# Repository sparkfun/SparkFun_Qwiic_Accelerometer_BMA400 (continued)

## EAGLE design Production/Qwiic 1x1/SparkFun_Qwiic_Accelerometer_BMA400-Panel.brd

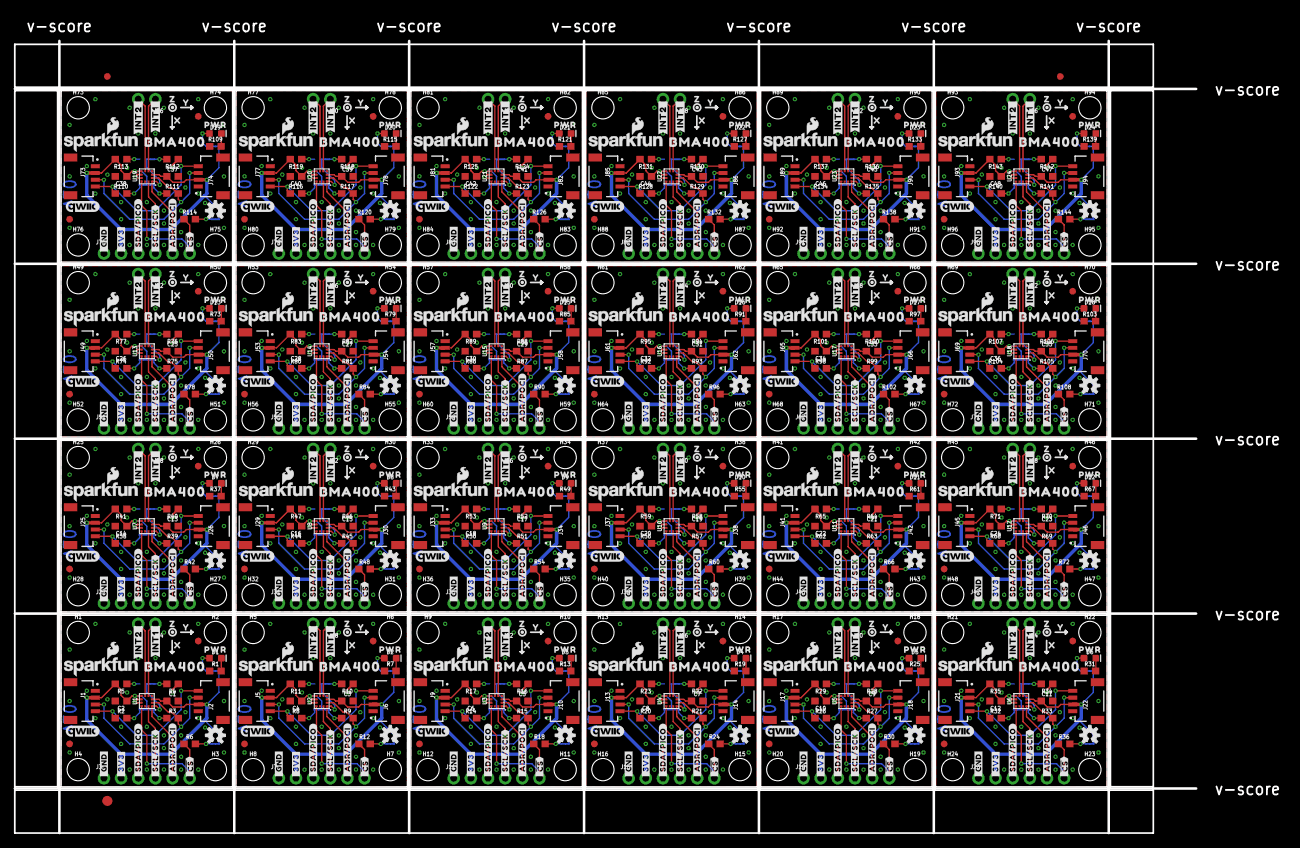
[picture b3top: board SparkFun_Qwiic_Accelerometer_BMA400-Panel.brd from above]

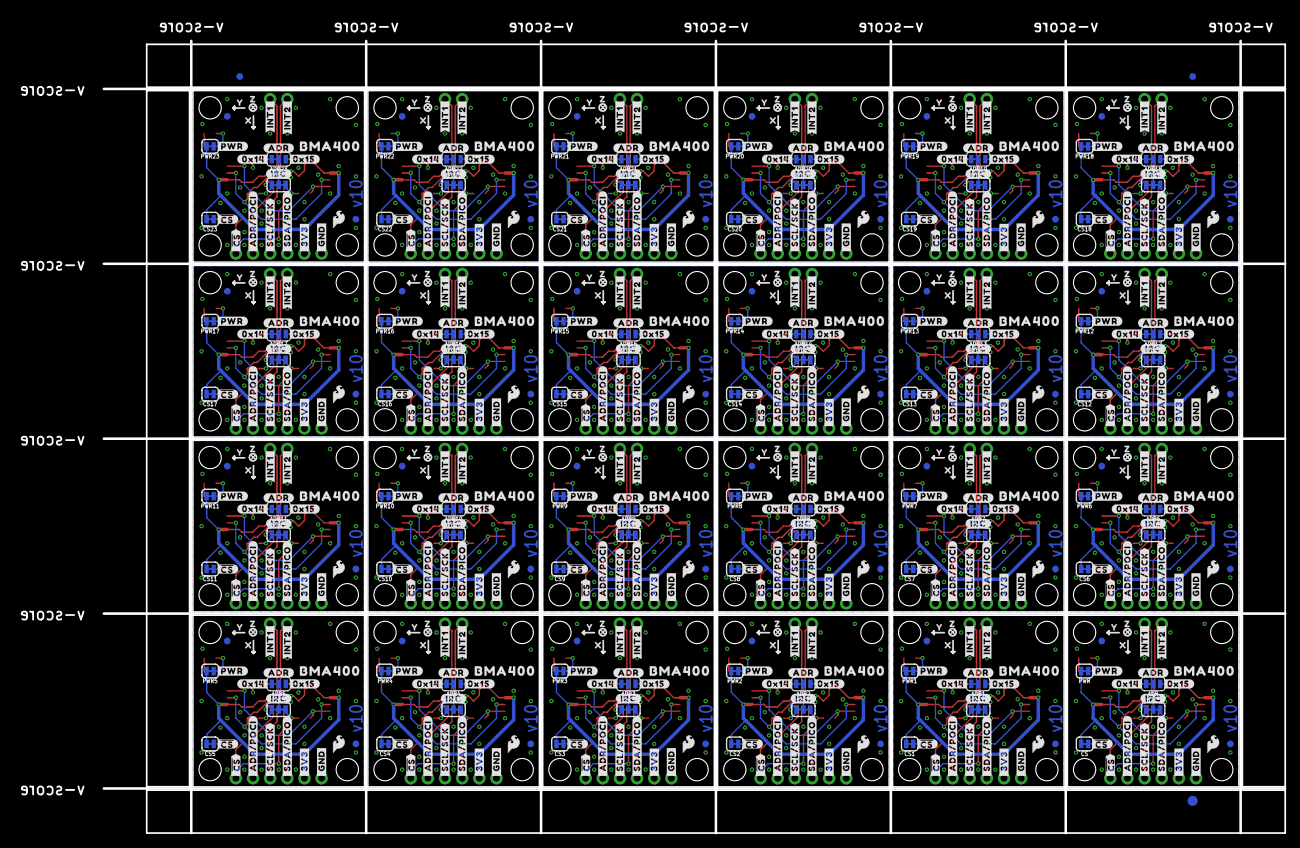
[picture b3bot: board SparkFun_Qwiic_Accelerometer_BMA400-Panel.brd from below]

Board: 2 copper layers, 175.0 x 117.3 mm, 1470 parts (603 on the bottom side), 360 nets.

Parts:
!CS!, !CS!1, !CS!2, !CS!3, !CS!4, !CS!5, !CS!6, !CS!7, !CS!8, !CS!9, !CS!10, !CS!11, !CS!12, !CS!13, !CS!14, !CS!15, !CS!16, !CS!17, !CS!18, !CS!19, !CS!20, !CS!21, !CS!22, !CS!23: JUMPER-SMT_2_NC_TRACE_SILK; SMT-JUMPER_2_NC_TRACE_SILK
ADR, ADR1, ADR2, ADR3, ADR4, ADR5, ADR6, ADR7, ADR8, ADR9, ADR10, ADR11, ADR12, ADR13, ADR14, ADR15, ADR16, ADR17, ADR18, ADR19, ADR20, ADR21, ADR22, ADR23: JUMPER-SMT_3_1-NC_TRACE_SILK; SMT-JUMPER_3_1-NC_TRACE_SILK
C1, C2, C3, C4, C5, C6, C7, C8, C9, C10, C11, C12, C13, C14, C15, C16, C17, C18, C19, C20, C21, C22, C23, C24, C25, C26, C27, C28, C29, C30, C31, C32, C33, C34, C35, C36, C37, C38, C39, C40, C41, C42, C43, C44, C45, C46, C47, C48: 0.1uF; 0603
D1, D2, D3, D4, D5, D6, D7, D8, D9, D10, D11, D12, D13, D14, D15, D16, D17, D18, D19, D20, D21, D22, D23, D24: RED; LED-0603
E$1, E$2, E$3, E$4: FIDUCIAL-1X2
E$5, E$6: FIDUCIAL-1.5X3
FD1, FD2, FD3, FD4, FD5, FD6, FD7, FD8, FD9, FD10, FD11, FD12, FD13, FD14, FD15, FD16, FD17, FD18, FD19, FD20, FD21, FD22, FD23, FD24, FD25, FD26, FD27, FD28, FD29, FD30, FD31, FD32, FD33, FD34, FD35, FD36, FD37, FD38, FD39, FD40, FD41, FD42, FD43, FD44, FD45, FD46, FD47, FD48, FD49, FD50, FD51, FD52, FD53, FD54, FD55, FD56, FD57, FD58, FD59, FD60, FD61, FD62, FD63, FD64, FD65, FD66, FD67, FD68, FD69, FD70, FD71, FD72, FD73, FD74, FD75, FD76, FD77, FD78, FD79, FD80, FD81, FD82, FD83, FD84, FD85, FD86, FD87, FD88, FD89, FD90, FD91, FD92, FD93, FD94, FD95, FD96: FIDUCIAL1X2; FIDUCIAL-1X2
H1, H2, H3, H4, H5, H6, H7, H8, H9, H10, H11, H12, H13, H14, H15, H16, H17, H18, H19, H20, H21, H22, H23, H24, H25, H26, H27, H28, H29, H30, H31, H32, H33, H34, H35, H36, H37, H38, H39, H40, H41, H42, H43, H44, H45, H46, H47, H48, H49, H50, H51, H52, H53, H54, H55, H56, H57, H58, H59, H60, H61, H62, H63, H64, H65, H66, H67, H68, H69, H70, H71, H72, H73, H74, H75, H76, H77, H78, H79, H80, H81, H82, H83, H84, H85, H86, H87, H88, H89, H90, H91, H92, H93, H94, H95, H96: STAND-OFF
I2C, I2C1, I2C2, I2C3, I2C4, I2C5, I2C6, I2C7, I2C8, I2C9, I2C10, I2C11, I2C12, I2C13, I2C14, I2C15, I2C16, I2C17, I2C18, I2C19, I2C20, I2C21, I2C22, I2C23: JUMPER-SMT_3_2-NC_TRACE_SILK; SMT-JUMPER_3_2-NC_TRACE_SILK
J1, J2, J5, J6, J9, J10, J13, J14, J17, J18, J21, J22, J25, J26, J29, J30, J33, J34, J37, J38, J41, J42, J45, J46, J49, J50, J53, J54, J57, J58, J61, J62, J65, J66, J69, J70, J73, J74, J77, J78, J81, J82, J85, J86, J89, J90, J93, J94: QWIIC_RIGHT_ANGLE; JST04_1MM_RA
J3, J7, J11, J15, J19, J23, J27, J31, J35, J39, J43, J47, J51, J55, J59, J63, J67, J71, J75, J79, J83, J87, J91, J95: 1X06_NO_SILK
J4, J8, J12, J16, J20, J24, J28, J32, J36, J40, J44, J48, J52, J56, J60, J64, J68, J72, J76, J80, J84, J88, J92, J96: 1X02_NO_SILK
LOGO1, LOGO4, LOGO7, LOGO10, LOGO13, LOGO16, LOGO19, LOGO22, LOGO25, LOGO28, LOGO31, LOGO34, LOGO37, LOGO40, LOGO43, LOGO46, LOGO49, LOGO52, LOGO55, LOGO58, LOGO61, LOGO64, LOGO67, LOGO70: QWIIC_LOGO_5MM; QWIIC_5MM
LOGO2, LOGO5, LOGO8, LOGO11, LOGO14, LOGO17, LOGO20, LOGO23, LOGO26, LOGO29, LOGO32, LOGO35, LOGO38, LOGO41, LOGO44, LOGO47, LOGO50, LOGO53, LOGO56, LOGO59, LOGO62, LOGO65, LOGO68, LOGO71: SFE_LOGO_NAME_FLAME.1_INCH; SFE_LOGO_NAME_FLAME_.1
LOGO3, LOGO6, LOGO9, LOGO12, LOGO15, LOGO18, LOGO21, LOGO24, LOGO27, LOGO30, LOGO33, LOGO36, LOGO39, LOGO42, LOGO45, LOGO48, LOGO51, LOGO54, LOGO57, LOGO60, LOGO63, LOGO66, LOGO69, LOGO72: OSHW-LOGOS; OSHW-LOGO-S
PWR, PWR1, PWR2, PWR3, PWR4, PWR5, PWR6, PWR7, PWR8, PWR9, PWR10, PWR11, PWR12, PWR13, PWR14, PWR15, PWR16, PWR17, PWR18, PWR19, PWR20, PWR21, PWR22, PWR23: JUMPER-SMT_2_NC_TRACE_SILK; SMT-JUMPER_2_NC_TRACE_SILK
R1, R7, R13, R19, R25, R31, R37, R43, R49, R55, R61, R67, R73, R79, R85, R91, R97, R103, R109, R115, R121, R127, R133, R139: 1k; 0603
R2, R3, R8, R9, R14, R15, R20, R21, R26, R27, R32, R33, R38, R39, R44, R45, R50, R51, R56, R57, R62, R63, R68, R69, R74, R75, R80, R81, R86, R87, R92, R93, R98, R99, R104, R105, R110, R111, R116, R117, R122, R123, R128, R129, R134, R135, R140, R141: 2.2k; 0603
R4, R5, R6, R10, R11, R12, R16, R17, R18, R22, R23, R24, R28, R29, R30, R34, R35, R36, R40, R41, R42, R46, R47, R48, R52, R53, R54, R58, R59, R60, R64, R65, R66, R70, R71, R72, R76, R77, R78, R82, R83, R84, R88, R89, R90, R94, R95, R96, R100, R101, R102, R106, R107, R108, R112, R113, R114, R118, R119, R120, R124, R125, R126, R130, R131, R132, R136, R137, R138, R142, R143, R144: 10k; 0603
U1, U2, U3, U4, U5, U6, U7, U8, U9, U10, U11, U12, U13, U14, U15, U16, U17, U18, U19, U20, U21, U22, U23, U24: BMA400
U$1, U$30, U$65, U$97, U$129, U$161, U$193, U$225, U$257, U$289, U$321, U$353, U$385, U$417, U$449, U$481, U$513, U$545, U$577, U$609, U$641, U$673, U$705, U$737: PWR0
U$2, U$34, U$59, U$62, U$91, U$94, U$123, U$126, U$155, U$158, U$187, U$190, U$219, U$222, U$251, U$254, U$283, U$286, U$315, U$318, U$347, U$350, U$379, U$382, U$411, U$414, U$443, U$446, U$475, U$478, U$507, U$510, U$539, U$542, U$571, U$574, U$603, U$606, U$635, U$638, U$667, U$670, U$699, U$702, U$731, U$734, U$763, U$766: X2114
U$3, U$35, U$60, U$63, U$92, U$95, U$124, U$127, U$156, U$159, U$188, U$191, U$220, U$223, U$252, U$255, U$284, U$287, U$316, U$319, U$348, U$351, U$380, U$383, U$412, U$415, U$444, U$447, U$476, U$479, U$508, U$511, U$540, U$543, U$572, U$575, U$604, U$607, U$636, U$639, U$668, U$671, U$700, U$703, U$732, U$735, U$764, U$767: Y2115
U$4, U$20, U$31, U$46, U$66, U$78, U$98, U$110, U$130, U$142, U$162, U$174, U$194, U$206, U$226, U$238, U$258, U$270, U$290, U$302, U$322, U$334, U$354, U$366, U$386, U$398, U$418, U$430, U$450, U$462, U$482, U$494, U$514, U$526, U$546, U$558, U$578, U$590, U$610, U$622, U$642, U$654, U$674, U$686, U$706, U$718, U$738, U$750: #INT1_#0
U$5, U$21, U$32, U$47, U$67, U$79, U$99, U$111, U$131, U$143, U$163, U$175, U$195, U$207, U$227, U$239, U$259, U$271, U$291, U$303, U$323, U$335, U$355, U$367, U$387, U$399, U$419, U$431, U$451, U$463, U$483, U$495, U$515, U$527, U$547, U$559, U$579, U$591, U$611, U$623, U$643, U$655, U$675, U$687, U$707, U$719, U$739, U$751: #INT2_#0
U$6, U$57, U$89, U$121, U$153, U$185, U$217, U$249, U$281, U$313, U$345, U$377, U$409, U$441, U$473, U$505, U$537, U$569, U$601, U$633, U$665, U$697, U$729, U$761: #_3V3#6
U$7, U$56, U$88, U$120, U$152, U$184, U$216, U$248, U$280, U$312, U$344, U$376, U$408, U$440, U$472, U$504, U$536, U$568, U$600, U$632, U$664, U$696, U$728, U$760: #_SDA#PICO#5
U$8, U$54, U$86, U$118, U$150, U$182, U$214, U$246, U$278, U$310, U$342, U$374, U$406, U$438, U$470, U$502, U$534, U$566, U$598, U$630, U$662, U$694, U$726, U$758: #_#CS##2
U$9, U$55, U$87, U$119, U$151, U$183, U$215, U$247, U$279, U$311, U$343, U$375, U$407, U$439, U$471, U$503, U$535, U$567, U$599, U$631, U$663, U$695, U$727, U$759: #_SCL#SCK#3
U$10, U$33, U$68, U$100, U$132, U$164, U$196, U$228, U$260, U$292, U$324, U$356, U$388, U$420, U$452, U$484, U$516, U$548, U$580, U$612, U$644, U$676, U$708, U$740: #_GND#0
U$11, U$37, U$69, U$101, U$133, U$165, U$197, U$229, U$261, U$293, U$325, U$357, U$389, U$421, U$453, U$485, U$517, U$549, U$581, U$613, U$645, U$677, U$709, U$741: #_3V3#0
U$12, U$38, U$70, U$102, U$134, U$166, U$198, U$230, U$262, U$294, U$326, U$358, U$390, U$422, U$454, U$486, U$518, U$550, U$582, U$614, U$646, U$678, U$710, U$742: #_SDA#PICO#0
U$13, U$39, U$71, U$103, U$135, U$167, U$199, U$231, U$263, U$295, U$327, U$359, U$391, U$423, U$455, U$487, U$519, U$551, U$583, U$615, U$647, U$679, U$711, U$743: #_SCL#SCK#0
U$14, U$40, U$72, U$104, U$136, U$168, U$200, U$232, U$264, U$296, U$328, U$360, U$392, U$424, U$456, U$488, U$520, U$552, U$584, U$616, U$648, U$680, U$712, U$744: #_ADR#POCI#0
U$15, U$41, U$73, U$105, U$137, U$169, U$201, U$233, U$265, U$297, U$329, U$361, U$393, U$425, U$457, U$489, U$521, U$553, U$585, U$617, U$649, U$681, U$713, U$745: #_#CS##0
U$16, U$42, U$74, U$106, U$138, U$170, U$202, U$234, U$266, U$298, U$330, U$362, U$394, U$426, U$458, U$490, U$522, U$554, U$586, U$618, U$650, U$682, U$714, U$746: #I2C#0
U$17, U$43, U$75, U$107, U$139, U$171, U$203, U$235, U$267, U$299, U$331, U$363, U$395, U$427, U$459, U$491, U$523, U$555, U$587, U$619, U$651, U$683, U$715, U$747: #ADR#0
U$18, U$44, U$76, U$108, U$140, U$172, U$204, U$236, U$268, U$300, U$332, U$364, U$396, U$428, U$460, U$492, U$524, U$556, U$588, U$620, U$652, U$684, U$716, U$748: #0X15#0
U$19, U$45, U$77, U$109, U$141, U$173, U$205, U$237, U$269, U$301, U$333, U$365, U$397, U$429, U$461, U$493, U$525, U$557, U$589, U$621, U$653, U$685, U$717, U$749: #0X14#0
U$22, U$48, U$80, U$112, U$144, U$176, U$208, U$240, U$272, U$304, U$336, U$368, U$400, U$432, U$464, U$496, U$528, U$560, U$592, U$624, U$656, U$688, U$720, U$752: #PWR#0
U$23, U$24, U$49, U$50, U$81, U$82, U$113, U$114, U$145, U$146, U$177, U$178, U$209, U$210, U$241, U$242, U$273, U$274, U$305, U$306, U$337, U$338, U$369, U$370, U$401, U$402, U$433, U$434, U$465, U$466, U$497, U$498, U$529, U$530, U$561, U$562, U$593, U$594, U$625, U$626, U$657, U$658, U$689, U$690, U$721, U$722, U$753, U$754: BMA4000
U$25, U$51, U$83, U$115, U$147, U$179, U$211, U$243, U$275, U$307, U$339, U$371, U$403, U$435, U$467, U$499, U$531, U$563, U$595, U$627, U$659, U$691, U$723, U$755: ##CS##0
U$26, U$52, U$84, U$116, U$148, U$180, U$212, U$244, U$276, U$308, U$340, U$372, U$404, U$436, U$468, U$500, U$532, U$564, U$596, U$628, U$660, U$692, U$724, U$756: SFE_LOGO_FLAME_.1
U$27, U$53, U$85, U$117, U$149, U$181, U$213, U$245, U$277, U$309, U$341, U$373, U$405, U$437, U$469, U$501, U$533, U$565, U$597, U$629, U$661, U$693, U$725, U$757: #_ADR#POCI#1
U$28, U$58, U$90, U$122, U$154, U$186, U$218, U$250, U$282, U$314, U$346, U$378, U$410, U$442, U$474, U$506, U$538, U$570, U$602, U$634, U$666, U$698, U$730, U$762: #_GND#6
U$29, U$36, U$61, U$64, U$93, U$96, U$125, U$128, U$157, U$160, U$189, U$192, U$221, U$224, U$253, U$256, U$285, U$288, U$317, U$320, U$349, U$352, U$381, U$384, U$413, U$416, U$445, U$448, U$477, U$480, U$509, U$512, U$541, U$544, U$573, U$576, U$605, U$608, U$637, U$640, U$669, U$672, U$701, U$704, U$733, U$736, U$765, U$768: Z2116

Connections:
3.3V: !CS!.2, C1.1, C2.1, I2C.2, J1.2, J2.2, J3.2, PWR.2, R5.2, U1.3, U1.7
3.3V1: !CS!1.2, C3.1, C4.1, I2C1.2, J5.2, J6.2, J7.2, PWR1.2, R11.2, U2.3, U2.7
3.3V2: !CS!2.2, C5.1, C6.1, I2C2.2, J9.2, J10.2, J11.2, PWR2.2, R17.2, U3.3, U3.7
3.3V3: !CS!3.2, C7.1, C8.1, I2C3.2, J13.2, J14.2, J15.2, PWR3.2, R23.2, U4.3, U4.7
3.3V4: !CS!4.2, C9.1, C10.1, I2C4.2, J17.2, J18.2, J19.2, PWR4.2, R29.2, U5.3, U5.7
3.3V5: !CS!5.2, C11.1, C12.1, I2C5.2, J21.2, J22.2, J23.2, PWR5.2, R35.2, U6.3, U6.7
3.3V6: !CS!6.2, C13.1, C14.1, I2C6.2, J25.2, J26.2, J27.2, PWR6.2, R41.2, U7.3, U7.7
3.3V7: !CS!7.2, C15.1, C16.1, I2C7.2, J29.2, J30.2, J31.2, PWR7.2, R47.2, U8.3, U8.7
3.3V8: !CS!8.2, C17.1, C18.1, I2C8.2, J33.2, J34.2, J35.2, PWR8.2, R53.2, U9.3, U9.7
3.3V9: !CS!9.2, C19.1, C20.1, I2C9.2, J37.2, J38.2, J39.2, PWR9.2, R59.2, U10.3, U10.7
3.3V10: !CS!10.2, C21.1, C22.1, I2C10.2, J41.2, J42.2, J43.2, PWR10.2, R65.2, U11.3, U11.7
3.3V11: !CS!11.2, C23.1, C24.1, I2C11.2, J45.2, J46.2, J47.2, PWR11.2, R71.2, U12.3, U12.7
3.3V12: !CS!12.2, C25.1, C26.1, I2C12.2, J49.2, J50.2, J51.2, PWR12.2, R77.2, U13.3, U13.7
3.3V13: !CS!13.2, C27.1, C28.1, I2C13.2, J53.2, J54.2, J55.2, PWR13.2, R83.2, U14.3, U14.7
3.3V14: !CS!14.2, C29.1, C30.1, I2C14.2, J57.2, J58.2, J59.2, PWR14.2, R89.2, U15.3, U15.7
3.3V15: !CS!15.2, C31.1, C32.1, I2C15.2, J61.2, J62.2, J63.2, PWR15.2, R95.2, U16.3, U16.7
3.3V16: !CS!16.2, C33.1, C34.1, I2C16.2, J65.2, J66.2, J67.2, PWR16.2, R101.2, U17.3, U17.7
3.3V17: !CS!17.2, C35.1, C36.1, I2C17.2, J69.2, J70.2, J71.2, PWR17.2, R107.2, U18.3, U18.7
3.3V18: !CS!18.2, C37.1, C38.1, I2C18.2, J73.2, J74.2, J75.2, PWR18.2, R113.2, U19.3, U19.7
3.3V19: !CS!19.2, C39.1, C40.1, I2C19.2, J77.2, J78.2, J79.2, PWR19.2, R119.2, U20.3, U20.7
3.3V20: !CS!20.2, C41.1, C42.1, I2C20.2, J81.2, J82.2, J83.2, PWR20.2, R125.2, U21.3, U21.7
3.3V21: !CS!21.2, C43.1, C44.1, I2C21.2, J85.2, J86.2, J87.2, PWR21.2, R131.2, U22.3, U22.7
3.3V22: !CS!22.2, C45.1, C46.1, I2C22.2, J89.2, J90.2, J91.2, PWR22.2, R137.2, U23.3, U23.7
3.3V23: !CS!23.2, C47.1, C48.1, I2C23.2, J93.2, J94.2, J95.2, PWR23.2, R143.2, U24.3, U24.7
!CS!: J3.6, R6.1, U1.10
!CS!1: J7.6, R12.1, U2.10
!CS!2: J11.6, R18.1, U3.10
!CS!3: J15.6, R24.1, U4.10
!CS!4: J19.6, R30.1, U5.10
!CS!5: J23.6, R36.1, U6.10
!CS!6: J27.6, R42.1, U7.10
!CS!7: J31.6, R48.1, U8.10
!CS!8: J35.6, R54.1, U9.10
!CS!9: J39.6, R60.1, U10.10
!CS!10: J43.6, R66.1, U11.10
!CS!11: J47.6, R72.1, U12.10
!CS!12: J51.6, R78.1, U13.10
!CS!13: J55.6, R84.1, U14.10
!CS!14: J59.6, R90.1, U15.10
!CS!15: J63.6, R96.1, U16.10
!CS!16: J67.6, R102.1, U17.10
!CS!17: J71.6, R108.1, U18.10
!CS!18: J75.6, R114.1, U19.10
!CS!19: J79.6, R120.1, U20.10
!CS!20: J83.6, R126.1, U21.10
!CS!21: J87.6, R132.1, U22.10
!CS!22: J91.6, R138.1, U23.10
!CS!23: J95.6, R144.1, U24.10
ADR/POCI: ADR.2, J3.5, U1.1
ADR/POCI1: ADR1.2, J7.5, U2.1
ADR/POCI2: ADR2.2, J11.5, U3.1
ADR/POCI3: ADR3.2, J15.5, U4.1
ADR/POCI4: ADR4.2, J19.5, U5.1
ADR/POCI5: ADR5.2, J23.5, U6.1
ADR/POCI6: ADR6.2, J27.5, U7.1
ADR/POCI7: ADR7.2, J31.5, U8.1
ADR/POCI8: ADR8.2, J35.5, U9.1
ADR/POCI9: ADR9.2, J39.5, U10.1
ADR/POCI10: ADR10.2, J43.5, U11.1
ADR/POCI11: ADR11.2, J47.5, U12.1
ADR/POCI12: ADR12.2, J51.5, U13.1
ADR/POCI13: ADR13.2, J55.5, U14.1
ADR/POCI14: ADR14.2, J59.5, U15.1
ADR/POCI15: ADR15.2, J63.5, U16.1
ADR/POCI16: ADR16.2, J67.5, U17.1
ADR/POCI17: ADR17.2, J71.5, U18.1
ADR/POCI18: ADR18.2, J75.5, U19.1
ADR/POCI19: ADR19.2, J79.5, U20.1
ADR/POCI20: ADR20.2, J83.5, U21.1
ADR/POCI21: ADR21.2, J87.5, U22.1
ADR/POCI22: ADR22.2, J91.5, U23.1
ADR/POCI23: ADR23.2, J95.5, U24.1
GND: C1.2, C2.2, J1.1, J2.1, J3.1, R1.1, R4.1, U1.8, U1.9
GND1: C3.2, C4.2, J5.1, J6.1, J7.1, R7.1, R10.1, U2.8, U2.9
GND2: C5.2, C6.2, J9.1, J10.1, J11.1, R13.1, R16.1, U3.8, U3.9
GND3: C7.2, C8.2, J13.1, J14.1, J15.1, R19.1, R22.1, U4.8, U4.9
GND4: C9.2, C10.2, J17.1, J18.1, J19.1, R25.1, R28.1, U5.8, U5.9
GND5: C11.2, C12.2, J21.1, J22.1, J23.1, R31.1, R34.1, U6.8, U6.9
GND6: C13.2, C14.2, J25.1, J26.1, J27.1, R37.1, R40.1, U7.8, U7.9
GND7: C15.2, C16.2, J29.1, J30.1, J31.1, R43.1, R46.1, U8.8, U8.9
GND8: C17.2, C18.2, J33.1, J34.1, J35.1, R49.1, R52.1, U9.8, U9.9
GND9: C19.2, C20.2, J37.1, J38.1, J39.1, R55.1, R58.1, U10.8, U10.9
GND10: C21.2, C22.2, J41.1, J42.1, J43.1, R61.1, R64.1, U11.8, U11.9
GND11: C23.2, C24.2, J45.1, J46.1, J47.1, R67.1, R70.1, U12.8, U12.9
GND12: C25.2, C26.2, J49.1, J50.1, J51.1, R73.1, R76.1, U13.8, U13.9
GND13: C27.2, C28.2, J53.1, J54.1, J55.1, R79.1, R82.1, U14.8, U14.9
GND14: C29.2, C30.2, J57.1, J58.1, J59.1, R85.1, R88.1, U15.8, U15.9
GND15: C31.2, C32.2, J61.1, J62.1, J63.1, R91.1, R94.1, U16.8, U16.9
GND16: C33.2, C34.2, J65.1, J66.1, J67.1, R97.1, R100.1, U17.8, U17.9
GND17: C35.2, C36.2, J69.1, J70.1, J71.1, R103.1, R106.1, U18.8, U18.9
GND18: C37.2, C38.2, J73.1, J74.1, J75.1, R109.1, R112.1, U19.8, U19.9
GND19: C39.2, C40.2, J77.1, J78.1, J79.1, R115.1, R118.1, U20.8, U20.9
GND20: C41.2, C42.2, J81.1, J82.1, J83.1, R121.1, R124.1, U21.8, U21.9
GND21: C43.2, C44.2, J85.1, J86.1, J87.1, R127.1, R130.1, U22.8, U22.9
GND22: C45.2, C46.2, J89.1, J90.1, J91.1, R133.1, R136.1, U23.8, U23.9
GND23: C47.2, C48.2, J93.1, J94.1, J95.1, R139.1, R142.1, U24.8, U24.9
INT1: J4.1, U1.5
INT2: J4.2, U1.6
INT3: J8.1, U2.5
INT4: J8.2, U2.6
INT5: J12.1, U3.5
INT6: J12.2, U3.6
INT7: J16.1, U4.5
INT8: J16.2, U4.6
INT9: J20.1, U5.5
INT10: J20.2, U5.6
INT11: J24.1, U6.5
INT12: J24.2, U6.6
INT13: J28.1, U7.5
INT14: J28.2, U7.6
INT15: J32.1, U8.5
INT16: J32.2, U8.6
INT17: J36.1, U9.5
INT18: J36.2, U9.6
INT19: J40.1, U10.5
INT20: J40.2, U10.6
INT21: J44.1, U11.5
INT22: J44.2, U11.6
INT23: J48.1, U12.5
INT24: J48.2, U12.6
INT25: J52.1, U13.5
INT26: J52.2, U13.6
INT27: J56.1, U14.5
INT28: J56.2, U14.6
INT29: J60.1, U15.5
INT30: J60.2, U15.6
INT31: J64.1, U16.5
INT32: J64.2, U16.6
INT33: J68.1, U17.5
INT34: J68.2, U17.6
INT35: J72.1, U18.5
INT36: J72.2, U18.6
INT37: J76.1, U19.5
INT38: J76.2, U19.6
INT39: J80.1, U20.5
INT40: J80.2, U20.6
INT41: J84.1, U21.5
INT42: J84.2, U21.6
INT43: J88.1, U22.5
INT44: J88.2, U22.6
INT45: J92.1, U23.5
INT46: J92.2, U23.6
INT47: J96.1, U24.5
INT48: J96.2, U24.6
unnamed: D1.A, PWR.1
unnamed: D1.C, R1.2
unnamed: I2C.3, R2.2
unnamed: I2C.1, R3.1
unnamed: ADR.1, R5.1
unnamed: ADR.3, R4.2
unnamed: !CS!.1, R6.2
unnamed: D2.C, R7.2
unnamed: I2C1.3, R8.2
unnamed: I2C1.1, R9.1
unnamed: ADR1.1, R11.1
unnamed: ADR1.3, R10.2
unnamed: D2.A, PWR1.1
unnamed: !CS!1.1, R12.2
unnamed: D3.C, R13.2
unnamed: I2C2.3, R14.2
unnamed: I2C2.1, R15.1
unnamed: ADR2.1, R17.1
unnamed: ADR2.3, R16.2
unnamed: D3.A, PWR2.1
unnamed: !CS!2.1, R18.2
unnamed: D4.C, R19.2
unnamed: I2C3.3, R20.2
unnamed: I2C3.1, R21.1
unnamed: ADR3.1, R23.1
unnamed: ADR3.3, R22.2
unnamed: D4.A, PWR3.1
unnamed: !CS!3.1, R24.2
unnamed: D5.C, R25.2
unnamed: I2C4.3, R26.2
unnamed: I2C4.1, R27.1
unnamed: ADR4.1, R29.1
unnamed: ADR4.3, R28.2
unnamed: D5.A, PWR4.1
unnamed: !CS!4.1, R30.2
unnamed: D6.C, R31.2
unnamed: I2C5.3, R32.2
unnamed: I2C5.1, R33.1
unnamed: ADR5.1, R35.1
unnamed: ADR5.3, R34.2
unnamed: D6.A, PWR5.1
unnamed: !CS!5.1, R36.2
unnamed: D7.C, R37.2
unnamed: I2C6.3, R38.2
unnamed: I2C6.1, R39.1
unnamed: ADR6.1, R41.1
unnamed: ADR6.3, R40.2
unnamed: D7.A, PWR6.1
unnamed: !CS!6.1, R42.2
unnamed: D8.C, R43.2
unnamed: I2C7.3, R44.2
unnamed: I2C7.1, R45.1
unnamed: ADR7.1, R47.1
unnamed: ADR7.3, R46.2
unnamed: D8.A, PWR7.1
unnamed: !CS!7.1, R48.2
unnamed: D9.C, R49.2
unnamed: I2C8.3, R50.2
unnamed: I2C8.1, R51.1
unnamed: ADR8.1, R53.1
unnamed: ADR8.3, R52.2
unnamed: D9.A, PWR8.1
unnamed: !CS!8.1, R54.2
unnamed: D10.C, R55.2
unnamed: I2C9.3, R56.2
unnamed: I2C9.1, R57.1
unnamed: ADR9.1, R59.1
unnamed: ADR9.3, R58.2
unnamed: D10.A, PWR9.1
unnamed: !CS!9.1, R60.2
unnamed: D11.C, R61.2
unnamed: I2C10.3, R62.2
unnamed: I2C10.1, R63.1
unnamed: ADR10.1, R65.1
unnamed: ADR10.3, R64.2
unnamed: D11.A, PWR10.1
unnamed: !CS!10.1, R66.2
unnamed: D12.C, R67.2
unnamed: I2C11.3, R68.2
unnamed: I2C11.1, R69.1
unnamed: ADR11.1, R71.1
unnamed: ADR11.3, R70.2
unnamed: D12.A, PWR11.1
unnamed: !CS!11.1, R72.2
unnamed: D13.C, R73.2
unnamed: I2C12.3, R74.2
unnamed: I2C12.1, R75.1
unnamed: ADR12.1, R77.1
unnamed: ADR12.3, R76.2
unnamed: D13.A, PWR12.1
unnamed: !CS!12.1, R78.2
unnamed: D14.C, R79.2
unnamed: I2C13.3, R80.2
unnamed: I2C13.1, R81.1
unnamed: ADR13.1, R83.1
unnamed: ADR13.3, R82.2
unnamed: D14.A, PWR13.1
unnamed: !CS!13.1, R84.2
unnamed: D15.C, R85.2
unnamed: I2C14.3, R86.2
unnamed: I2C14.1, R87.1
unnamed: ADR14.1, R89.1
unnamed: ADR14.3, R88.2
unnamed: D15.A, PWR14.1
unnamed: !CS!14.1, R90.2
unnamed: D16.C, R91.2
unnamed: I2C15.3, R92.2
unnamed: I2C15.1, R93.1
unnamed: ADR15.1, R95.1
unnamed: ADR15.3, R94.2
unnamed: D16.A, PWR15.1
unnamed: !CS!15.1, R96.2
unnamed: D17.C, R97.2
unnamed: I2C16.3, R98.2
unnamed: I2C16.1, R99.1
unnamed: ADR16.1, R101.1
unnamed: ADR16.3, R100.2
unnamed: D17.A, PWR16.1
unnamed: !CS!16.1, R102.2
unnamed: D18.C, R103.2
unnamed: I2C17.3, R104.2
unnamed: I2C17.1, R105.1
unnamed: ADR17.1, R107.1
unnamed: ADR17.3, R106.2
unnamed: D18.A, PWR17.1
unnamed: !CS!17.1, R108.2
unnamed: D19.C, R109.2
unnamed: I2C18.3, R110.2
unnamed: I2C18.1, R111.1
unnamed: ADR18.1, R113.1
unnamed: ADR18.3, R112.2
unnamed: D19.A, PWR18.1
unnamed: !CS!18.1, R114.2
unnamed: D20.C, R115.2
unnamed: I2C19.3, R116.2
unnamed: I2C19.1, R117.1
unnamed: ADR19.1, R119.1
unnamed: ADR19.3, R118.2
unnamed: D20.A, PWR19.1
unnamed: !CS!19.1, R120.2
unnamed: D21.C, R121.2
unnamed: I2C20.3, R122.2
unnamed: I2C20.1, R123.1
unnamed: ADR20.1, R125.1
unnamed: ADR20.3, R124.2
unnamed: D21.A, PWR20.1
unnamed: !CS!20.1, R126.2
unnamed: D22.C, R127.2
unnamed: I2C21.3, R128.2
unnamed: I2C21.1, R129.1
unnamed: ADR21.1, R131.1
unnamed: ADR21.3, R130.2
unnamed: D22.A, PWR21.1
unnamed: !CS!21.1, R132.2
unnamed: D23.C, R133.2
unnamed: I2C22.3, R134.2
unnamed: I2C22.1, R135.1
unnamed: ADR22.1, R137.1
unnamed: ADR22.3, R136.2
unnamed: D23.A, PWR22.1
unnamed: !CS!22.1, R138.2
unnamed: D24.C, R139.2
unnamed: I2C23.3, R140.2
unnamed: I2C23.1, R141.1
unnamed: ADR23.1, R143.1
unnamed: ADR23.3, R142.2
unnamed: D24.A, PWR23.1
unnamed: !CS!23.1, R144.2
SCL/SCK: J1.4, J2.4, J3.4, R2.1, U1.12
SCL/SCK1: J5.4, J6.4, J7.4, R8.1, U2.12
SCL/SCK2: J9.4, J10.4, J11.4, R14.1, U3.12
SCL/SCK3: J13.4, J14.4, J15.4, R20.1, U4.12
SCL/SCK4: J17.4, J18.4, J19.4, R26.1, U5.12
SCL/SCK5: J21.4, J22.4, J23.4, R32.1, U6.12
SCL/SCK6: J25.4, J26.4, J27.4, R38.1, U7.12
SCL/SCK7: J29.4, J30.4, J31.4, R44.1, U8.12
SCL/SCK8: J33.4, J34.4, J35.4, R50.1, U9.12
SCL/SCK9: J37.4, J38.4, J39.4, R56.1, U10.12
SCL/SCK10: J41.4, J42.4, J43.4, R62.1, U11.12
SCL/SCK11: J45.4, J46.4, J47.4, R68.1, U12.12
SCL/SCK12: J49.4, J50.4, J51.4, R74.1, U13.12
SCL/SCK13: J53.4, J54.4, J55.4, R80.1, U14.12
SCL/SCK14: J57.4, J58.4, J59.4, R86.1, U15.12
SCL/SCK15: J61.4, J62.4, J63.4, R92.1, U16.12
SCL/SCK16: J65.4, J66.4, J67.4, R98.1, U17.12
SCL/SCK17: J69.4, J70.4, J71.4, R104.1, U18.12
SCL/SCK18: J73.4, J74.4, J75.4, R110.1, U19.12
SCL/SCK19: J77.4, J78.4, J79.4, R116.1, U20.12
SCL/SCK20: J81.4, J82.4, J83.4, R122.1, U21.12
SCL/SCK21: J85.4, J86.4, J87.4, R128.1, U22.12
SCL/SCK22: J89.4, J90.4, J91.4, R134.1, U23.12
SCL/SCK23: J93.4, J94.4, J95.4, R140.1, U24.12
SDA/PICO: J1.3, J2.3, J3.3, R3.2, U1.2
SDA/PICO1: J5.3, J6.3, J7.3, R9.2, U2.2
SDA/PICO2: J9.3, J10.3, J11.3, R15.2, U3.2
SDA/PICO3: J13.3, J14.3, J15.3, R21.2, U4.2
SDA/PICO4: J17.3, J18.3, J19.3, R27.2, U5.2
SDA/PICO5: J21.3, J22.3, J23.3, R33.2, U6.2
SDA/PICO6: J25.3, J26.3, J27.3, R39.2, U7.2
SDA/PICO7: J29.3, J30.3, J31.3, R45.2, U8.2
SDA/PICO8: J33.3, J34.3, J35.3, R51.2, U9.2
SDA/PICO9: J37.3, J38.3, J39.3, R57.2, U10.2
SDA/PICO10: J41.3, J42.3, J43.3, R63.2, U11.2
SDA/PICO11: J45.3, J46.3, J47.3, R69.2, U12.2
SDA/PICO12: J49.3, J50.3, J51.3, R75.2, U13.2
SDA/PICO13: J53.3, J54.3, J55.3, R81.2, U14.2
SDA/PICO14: J57.3, J58.3, J59.3, R87.2, U15.2
SDA/PICO15: J61.3, J62.3, J63.3, R93.2, U16.2
SDA/PICO16: J65.3, J66.3, J67.3, R99.2, U17.2
SDA/PICO17: J69.3, J70.3, J71.3, R105.2, U18.2
SDA/PICO18: J73.3, J74.3, J75.3, R111.2, U19.2
SDA/PICO19: J77.3, J78.3, J79.3, R117.2, U20.2
SDA/PICO20: J81.3, J82.3, J83.3, R123.2, U21.2
SDA/PICO21: J85.3, J86.3, J87.3, R129.2, U22.2
SDA/PICO22: J89.3, J90.3, J91.3, R135.2, U23.2
SDA/PICO23: J93.3, J94.3, J95.3, R141.2, U24.2

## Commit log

2022-09-13 Add datasheet
2022-09-13 Create BMA400 library file
2022-09-13 Create initial 1x1 schematic and board
2022-09-13 Create initial micro schematic and board
2022-09-14 Design review updates
    Add BMA400 voltage range to schematics
    Add designer name to boards' tDocu
    Add measures to 1x1
    Adjust traces of micro
2022-09-14 Design review updates
    Reduce silk labels on top side of 1x1
    Adjust position of "BMA400" top silk of Micro
    Rotate PWR jumper of Micro
2022-09-14 Design review updates
    Fix I2C address table
    Add "default" to I2C address table
    Approve jumper overlap errors
2022-09-14 Add units to measures
2022-09-14 Change default I2C address
2022-09-15 Add PROD_ID and description to BMA400
2022-10-10 Add axes labels
2022-10-10 Update version number to v10
2022-10-13 Design review updates
    Move fiducials on Micro to be diagonal
    Add extra GND vias to Micro
2022-10-13 Add v10 production files
2022-10-20 Add text about 22AWG wires to Micro schematic
2022-12-06 Update README.md
    Update README.md for release.
2022-12-06 Update README.md
    Fixing typos.
2023-03-28 Remove library file
    Part is in SFE Eagle library, update part in design
